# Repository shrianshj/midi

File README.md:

# Midi Keyboard!!!
A MIDI keyboard made for Hack Club Half Life, with a few small customizations.
(You can't see the silkscreens, but they're there).

# In the PCB editor...

It contains 2 sliding sensors, and 7 customizable buttons. You can program it to act like drums, a piano, and you can use the 3 buttons for custom actions, like the RGB neopixels. The rotary potentiometer can be used for controlling the volume. In future versions, I will make it so you don't have to connect it to a computer and there will be a speaker on the board. I will also add a screen so you can program the sounds, buttons, etc.

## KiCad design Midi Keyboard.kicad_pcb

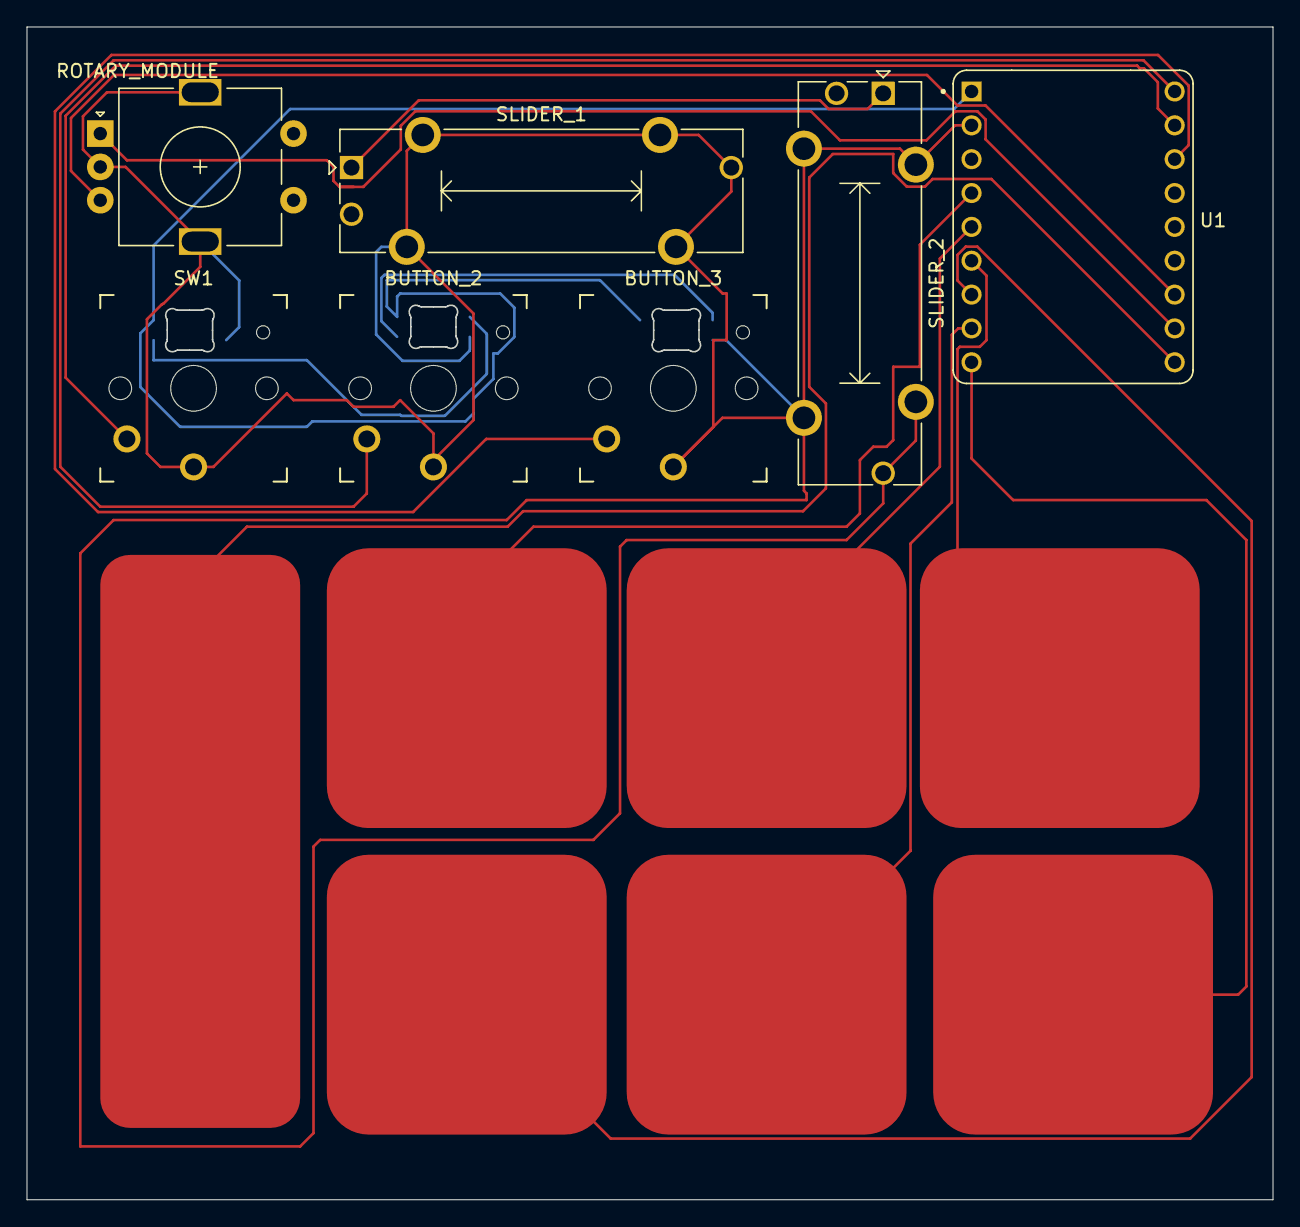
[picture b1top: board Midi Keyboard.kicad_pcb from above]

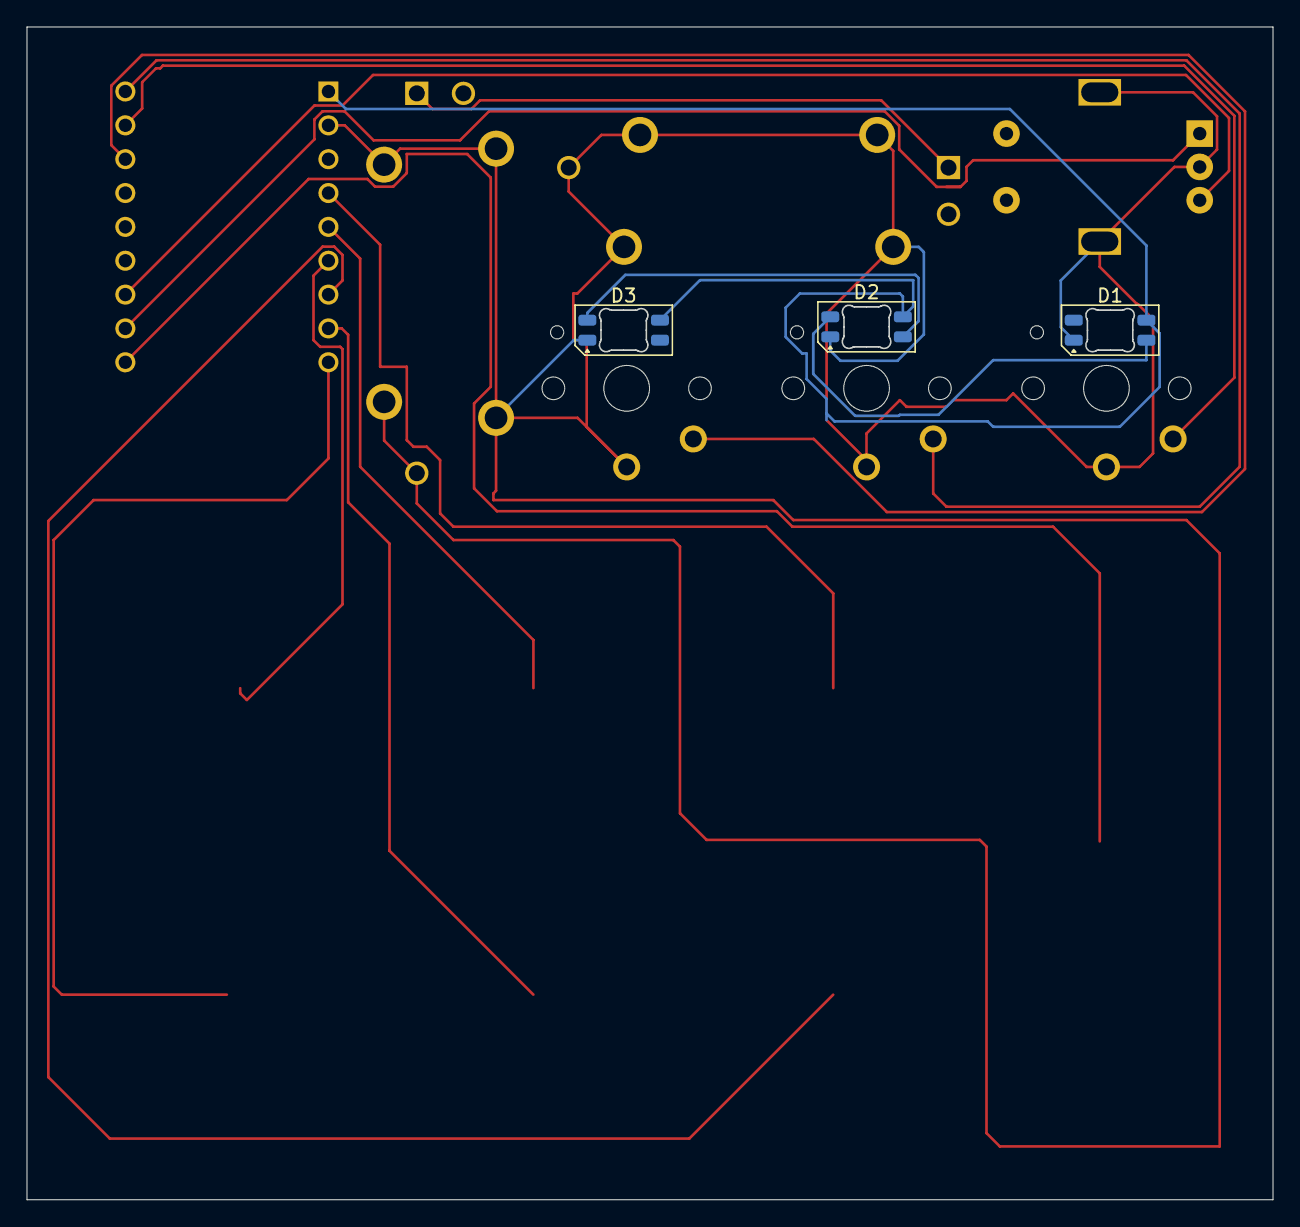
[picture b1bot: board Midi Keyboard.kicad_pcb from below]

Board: 2 copper layers, 93.5 x 88.0 mm, 11 parts (3 on the bottom side), 17 nets.

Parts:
BUTTON_2, BUTTON_3: SW_Push; Kailh Choc Low-Profile Switches
D1, D2, D3: SK6812MINI-E; LED_SK6812MINI-E_3.2x2.8mm_P1.5mm_ReverseMount
J1: Capacitive Touch Sensor; Capacitive_Keys
ROTARY_MODULE: BUTTON_1; RotaryEncoder_Alps_EC11E-Switch_Vertical_H20mm
SLIDER_1, SLIDER_2: RV1 Slider; Potentiometer_Bourns_PTA1543_Single_Slide
SW1: SW_Push; Kailh Choc Low-Profile Switches
U1: Waveshare ESP32 Microcontroller; Waveshare ESP32-S3-Zero

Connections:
+3V3: SLIDER_1.1, SLIDER_2.1
+5V: D1.3 (VDD), D2.3 (VDD), D3.3 (VDD), U1.5V
/ENC1_A: ROTARY_MODULE.A, U1.8 (GP8)
/ENC1_B: ROTARY_MODULE.B, U1.9 (GP9)
/SWITCH1: SW1.2, U1.RX
/SWITCH2: BUTTON_2.2, U1.TX
/SWITCH3: BUTTON_3.2, U1.13 (GP13)
/TOUCH1: J1.1, U1.1 (GP1)
/TOUCH2: J1.2, U1.2 (GP2)
/TOUCH3: J1.3, U1.3 (GP3)
/TOUCH4: J1.4, U1.4 (GP4)
/TOUCH5: J1.5, U1.5 (GP5)
/TOUCH6: J1.6, U1.6 (GP6)
/TOUCH7: J1.7, U1.7 (GP7)
GND: BUTTON_2.1, BUTTON_3.1, D1.1 (VSS), D2.1 (VSS), D3.1 (VSS), ROTARY_MODULE.C, ROTARY_MODULE.MP, SLIDER_1.3, SLIDER_1.MP (MountPin), SLIDER_2.3, SLIDER_2.MP (MountPin), SW1.1, U1.GND
unnamed: D1.4 (DOUT), D2.2 (DIN)
unnamed: D2.4 (DOUT), D3.2 (DIN)
